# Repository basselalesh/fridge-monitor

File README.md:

#Fridge Monitor

The Arduino-HDK Shield was a prototype that later became a ready-for-production PCB that can be mounted on the WNC M18Q2 model for an LTE connection using AT Commands, UART, TDP sockets, and the AT&T M2X API. It was the end-of-internship project by me that utilized the different tests and mini-projects that were tackled over the summer and combined everything that was learned into a comprehensive, user-friendly project. The shield is a 2-layer PCB that containts the wiring for an Arduino Pro Mini and an Adafruit 4-bit Bi-Directional Level Shifter to the Hardware Development Kit (HDK) from WNC & their Qualcomm's M18Q2 chipset. 

2.0.0 code includes: Set Time option, Posting every 1-1:30 minutes (depending on door closing and opening), Uses PIN0 and PIN1 for Hardware Serial UART communication, Reads from pins 5, 6, and 7 for sensor info and M2X
Pin 7 uses Wire and oneWire (based on I2C protocol) to post temperature data using a Dallas temperature sensor. Pins 5 and 6 use digitalRead to read IR sensors. 

Included in this project is the Arduino Pro Mini code that was used to control the HDK and the schematic and board files for the PCB.

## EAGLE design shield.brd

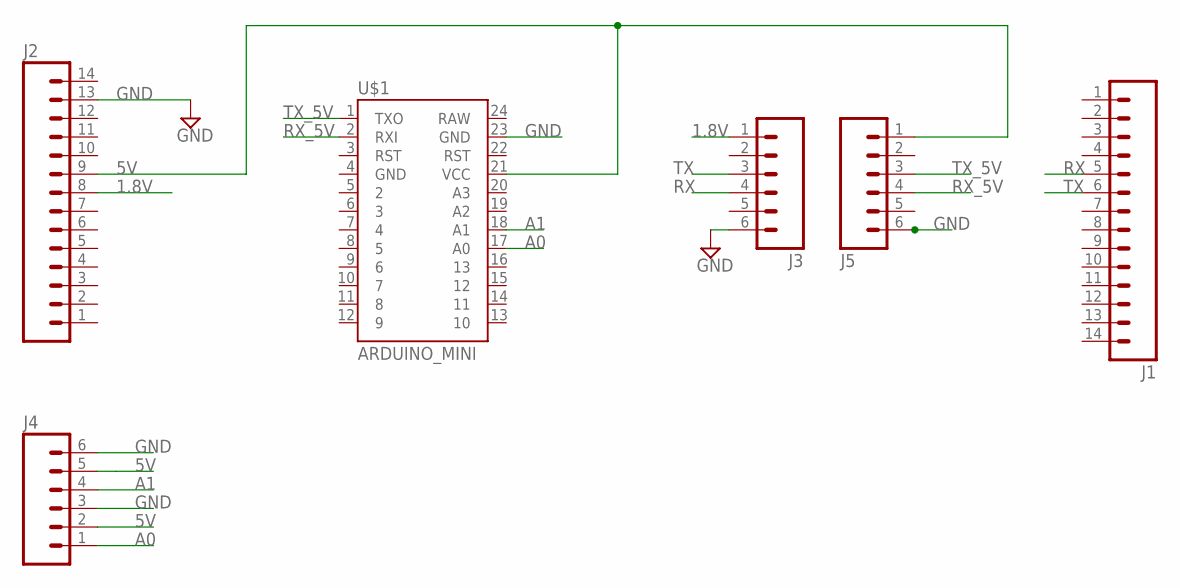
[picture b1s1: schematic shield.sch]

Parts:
J1, J2: M14LONGPADS; 1X14-LONGPADS
J3, J4, J5: M06LONGPADS; 1X06_LONGPADS
U$1: ARDUINO_MINI

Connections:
1.8V: J2.8, J3.1
5V: J2.9, J4.2, J4.5, J5.1, U$1.21 (VCC)
A0: J4.1, U$1.17 (A0)
A1: J4.4, U$1.18 (A1)
GND: J2.13, J3.6, J4.3, J4.6, J5.6, U$1.23 (GND)
RX: J1.5, J3.4
RX_5V: J5.4, U$1.2 (RXI)
TX: J1.6, J3.3
TX_5V: J5.3, U$1.1 (TXO)

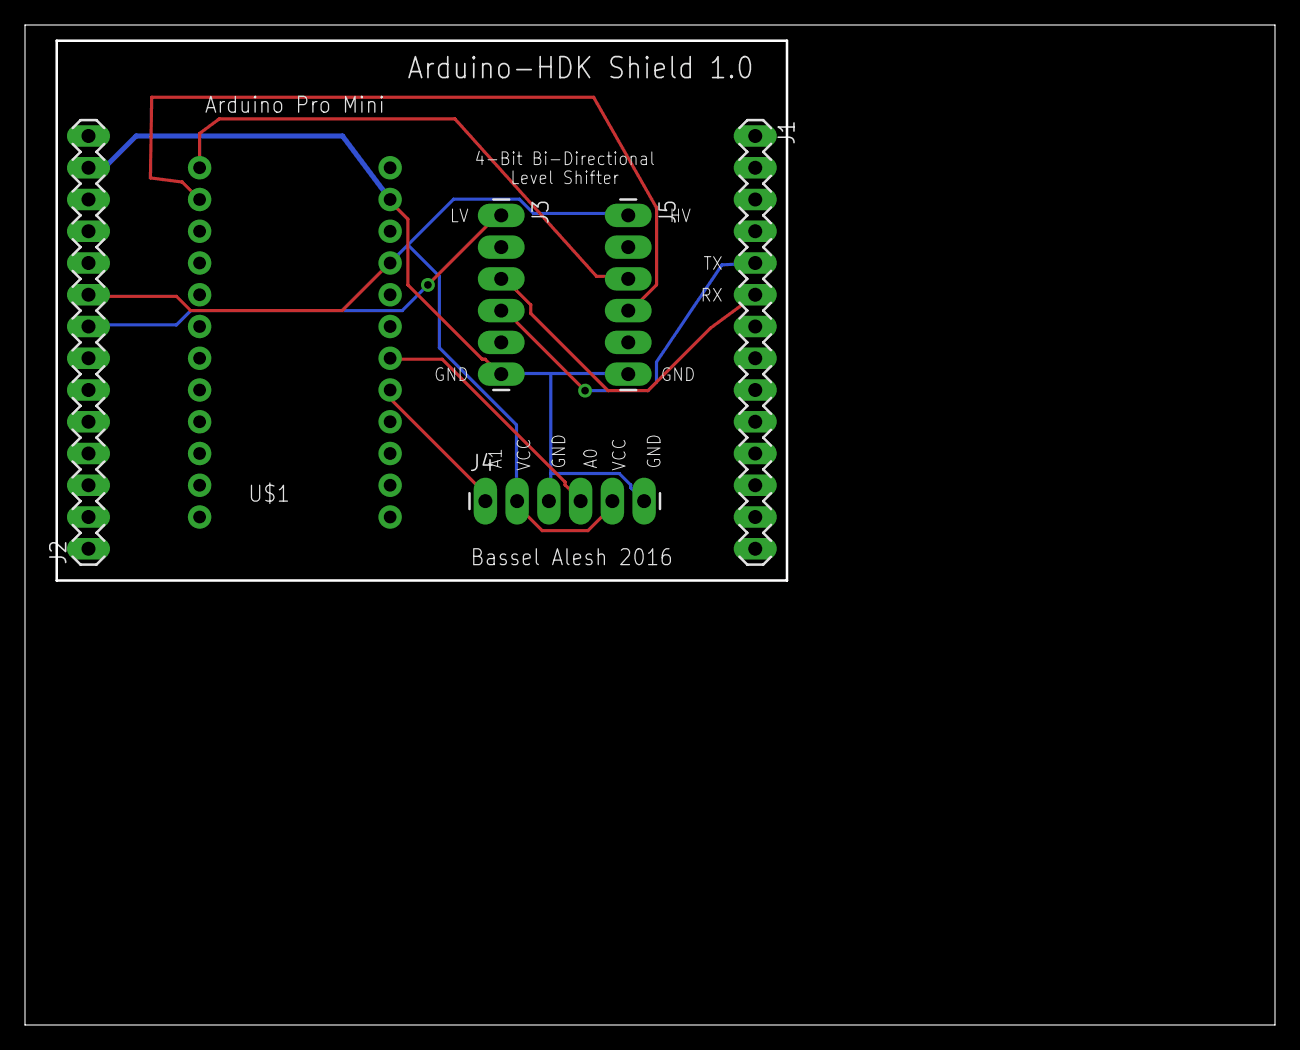
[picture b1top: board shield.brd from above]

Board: 2 copper layers, 99.8 x 79.8 mm, 6 parts (0 on the bottom side), 9 nets.

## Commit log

2016-08-17 Fridge Temperature versus Door Openings
    Code used for the Arduino to Hardware Development Kit (HDK) shield.
2016-08-17 Rename arduinoHDKtest_FridgeSensorProject_Version_1.ino to fridge_monitor
2016-08-17 Rename fridge_monitor to fridge-arduino
2016-08-17 Rename fridge-arduino to arduino_code_2.0.0
2016-08-17 Rename arduino_code_2.0.0 to arduino-code
2016-08-17 Rename finalHDKShield.brd to shield.brd
2016-08-17 Rename finalHDKShield.sch to shield.sch
2018-05-31 Rename arduino-code to arduino-code.ino

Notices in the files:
parts and their libraries:
SparkFun-Connectors: Licensing: Creative Commons ShareAlike 4.0 International - https://creativecommons.org/licenses/by-sa/4.0
